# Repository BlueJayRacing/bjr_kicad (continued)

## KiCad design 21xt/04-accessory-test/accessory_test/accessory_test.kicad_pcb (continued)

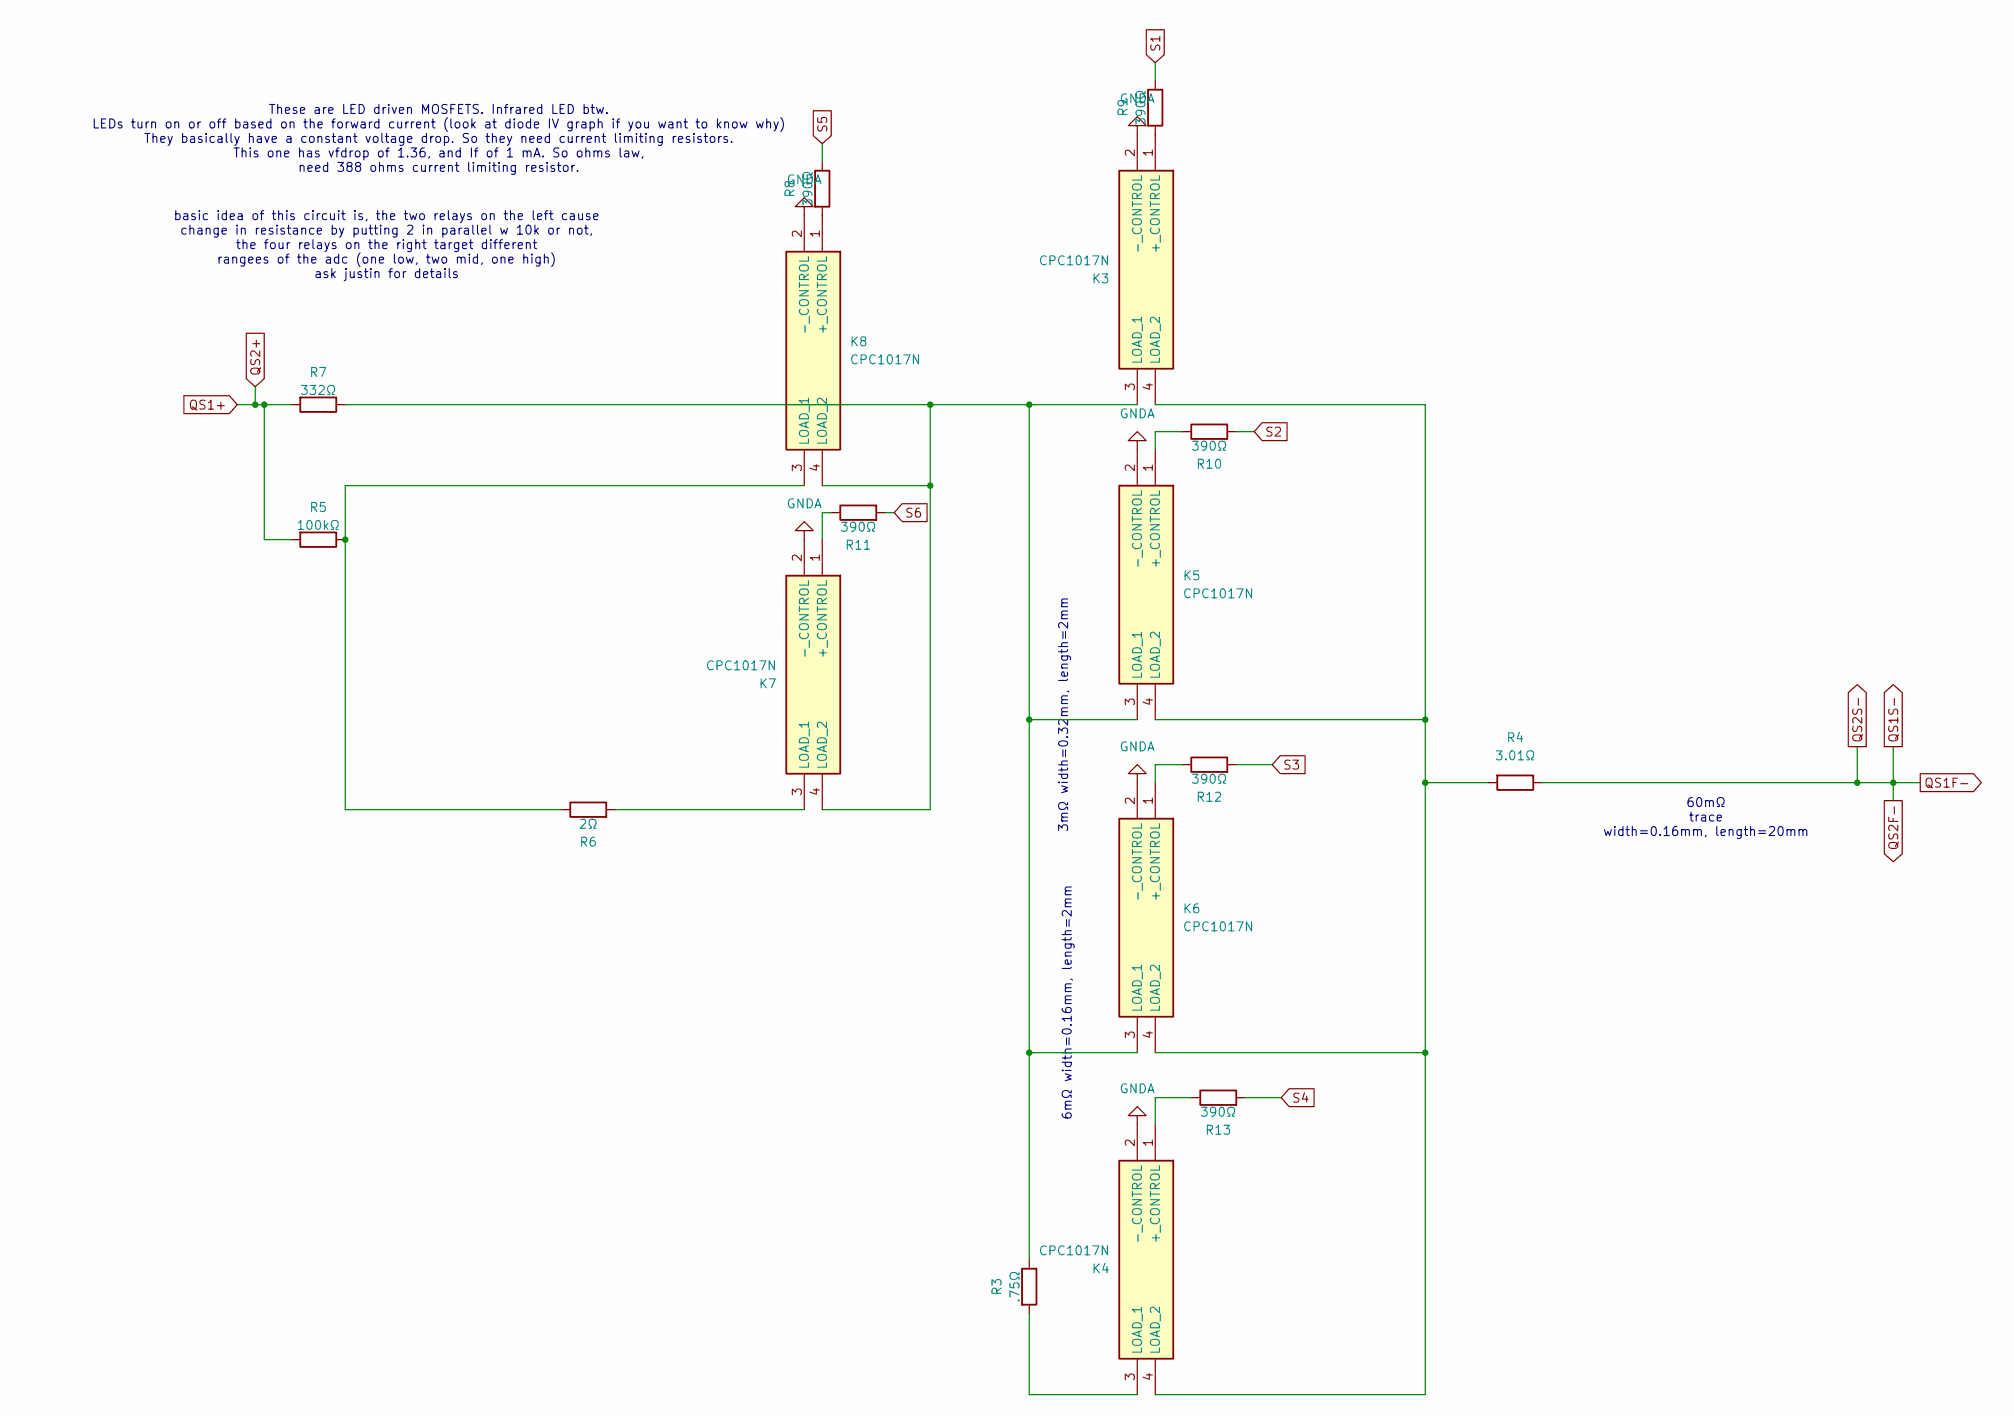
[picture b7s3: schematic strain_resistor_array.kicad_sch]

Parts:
K3, K4, K5, K6, K7, K8: CPC1017N; Mouser Part Number 849-CPC1017N
R3: .75Ω; R_0603_1608Metric
R4: 3.01Ω; R_1206_3216Metric
R5: 100kΩ; R_0603_1608Metric
R6: 2Ω; R_0603_1608Metric
R7: 332Ω; R_0402_1005Metric
R8, R9, R10, R11, R12, R13: 390Ω; R_0603_1608Metric

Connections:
GNDA: K3.2 (-_CONTROL), K4.2 (-_CONTROL), K5.2 (-_CONTROL), K6.2 (-_CONTROL), K7.2 (-_CONTROL), K8.2 (-_CONTROL); also elsewhere on the board
unnamed: K3.1 (+_CONTROL), R9.2
unnamed: K3.3 (LOAD_1), K5.3 (LOAD_1), K6.3 (LOAD_1), K7.4 (LOAD_2), K8.4 (LOAD_2), R3.1, R7.1
unnamed: K3.4 (LOAD_2), K4.4 (LOAD_2), K5.4 (LOAD_2), K6.4 (LOAD_2), R4.2
unnamed: K4.1 (+_CONTROL), R13.1
unnamed: K4.3 (LOAD_1), R3.2
unnamed: K5.1 (+_CONTROL), R10.1
unnamed: K6.1 (+_CONTROL), R12.1
unnamed: K7.1 (+_CONTROL), R11.1
unnamed: K7.3 (LOAD_1), R6.2
unnamed: K8.1 (+_CONTROL), R8.2
unnamed: K8.3 (LOAD_1), R5.1, R6.1
QS1+: R5.2, R7.2; also elsewhere on the board
QS1F-: R4.1; also elsewhere on the board
S1: R9.1; also elsewhere on the board
S2: R10.2; also elsewhere on the board
S3: R12.2; also elsewhere on the board
S4: R13.2; also elsewhere on the board
S5: R8.1; also elsewhere on the board
S6: R11.2; also elsewhere on the board

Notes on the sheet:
60mΩ trace width=0.16mm, length=20mm
6mΩ width=0.16mm, length=2mm
These are LED driven MOSFETS. Infrared LED btw. LEDs turn on or off based on the forward current (look at diode IV graph if you want to know why) They basically have a constant voltage drop. So they need current limiting resistors. This one has vfdrop of 1.36, and If of 1 mA. So ohms law, need 388 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
basic idea of this circuit is, the two relays on the left cause change in resistance by putting 2 in parallel w 10k or not, the four relays on the right target different rangees of the adc (one low, two mid, one high) ask justin for details
3mΩ width=0.32mm, length=2mm

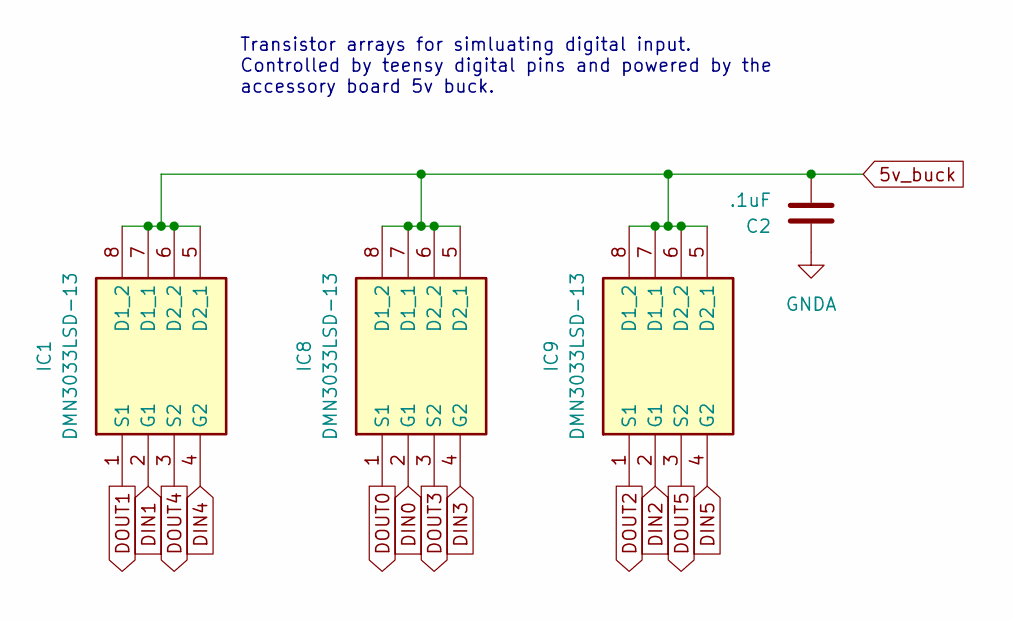
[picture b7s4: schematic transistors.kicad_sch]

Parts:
C2: .1uF; C_0603_1608Metric
IC1, IC8, IC9: DMN3033LSD-13; DMN3033LSD; Mouser Part Number 621-DMN3033LSD-13

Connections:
5v_buck: C2.2, IC1.5 (D2_1), IC1.6 (D2_2), IC1.7 (D1_1), IC1.8 (D1_2), IC8.5 (D2_1), IC8.6 (D2_2), IC8.7 (D1_1), IC8.8 (D1_2), IC9.5 (D2_1), IC9.6 (D2_2), IC9.7 (D1_1), IC9.8 (D1_2); also elsewhere on the board
CS_acc: IC8.3 (S2); also elsewhere on the board
DIN0: IC8.2 (G1); also elsewhere on the board
DIN1: IC1.2 (G1); also elsewhere on the board
DIN2: IC9.2 (G1); also elsewhere on the board
DIN3: IC8.4 (G2); also elsewhere on the board
DIN4: IC1.4 (G2); also elsewhere on the board
DIN5: IC9.4 (G2); also elsewhere on the board
DOUT0: IC8.1 (S1); also elsewhere on the board
DOUT1: IC1.1 (S1); also elsewhere on the board
DOUT2: IC9.1 (S1); also elsewhere on the board
DOUT4: IC1.3 (S2); also elsewhere on the board
DOUT5: IC9.3 (S2); also elsewhere on the board
GNDA: C2.1; also elsewhere on the board

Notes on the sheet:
Transistor arrays for simluating digital input. Controlled by teensy digital pins and powered by the accessory board 5v buck.

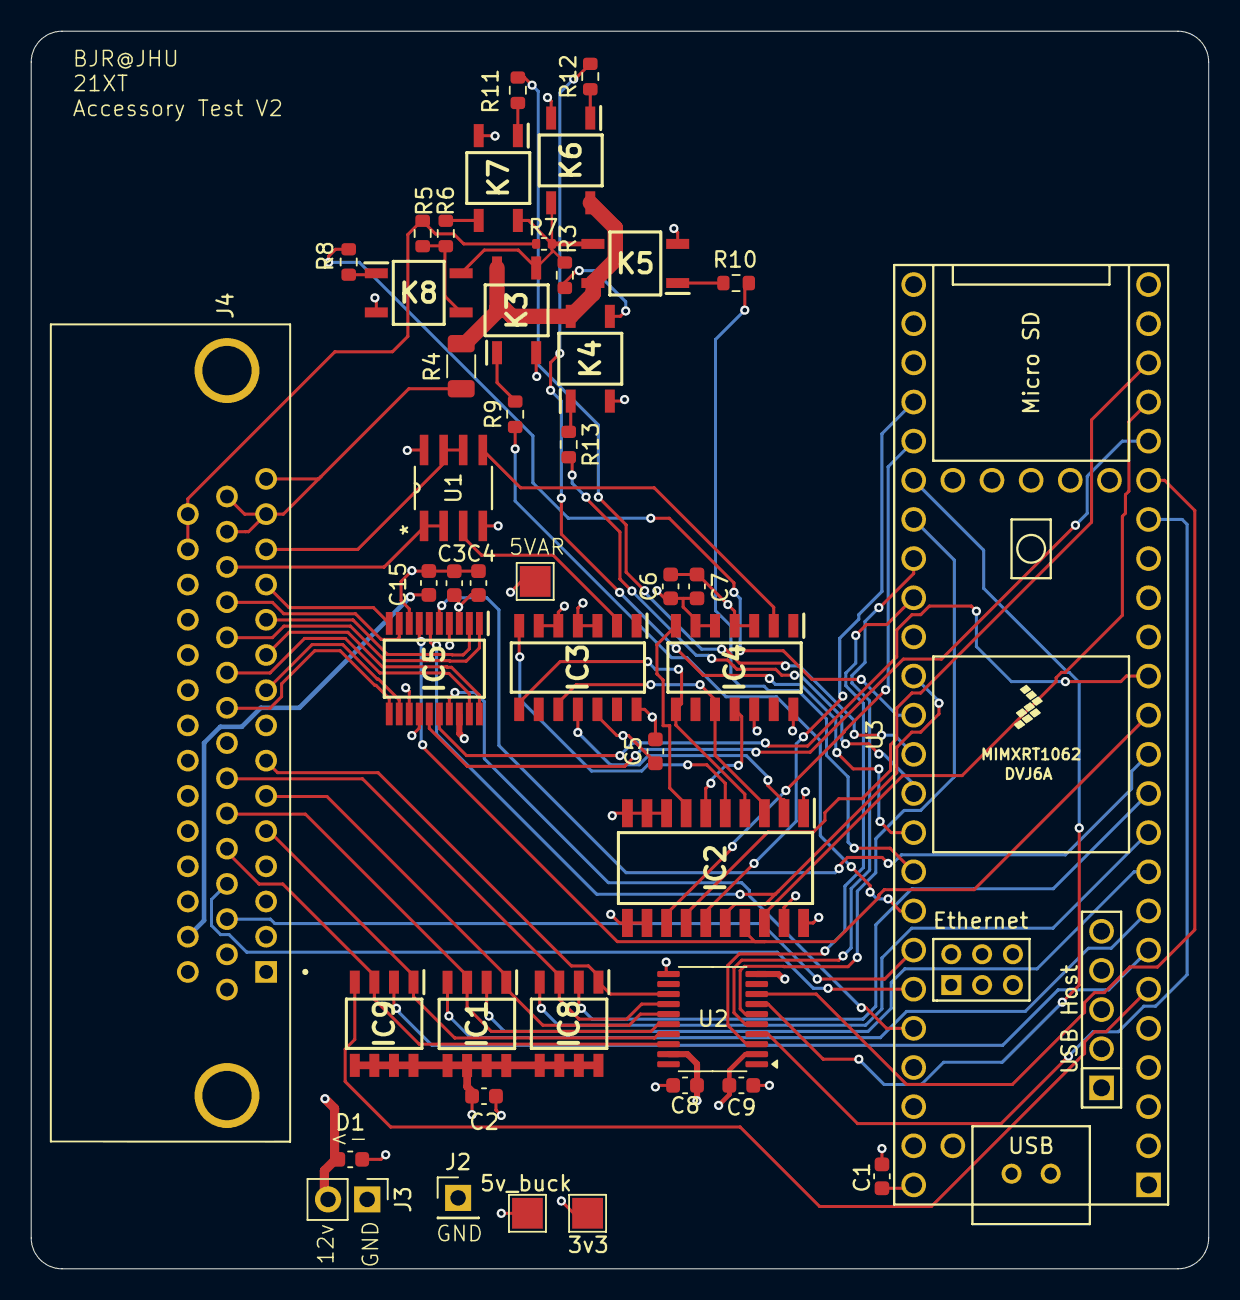
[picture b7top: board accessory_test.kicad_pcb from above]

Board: 4 copper layers, 76.4 x 80.3 mm, 44 parts (0 on the bottom side), 72 nets.

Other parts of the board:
3v3, 5v_buck: TestPoint; TestPoint_Pad_2.0x2.0mm

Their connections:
3v3: 3v3.1; also elsewhere on the board
5v_buck: 5v_buck.1; also elsewhere on the board
